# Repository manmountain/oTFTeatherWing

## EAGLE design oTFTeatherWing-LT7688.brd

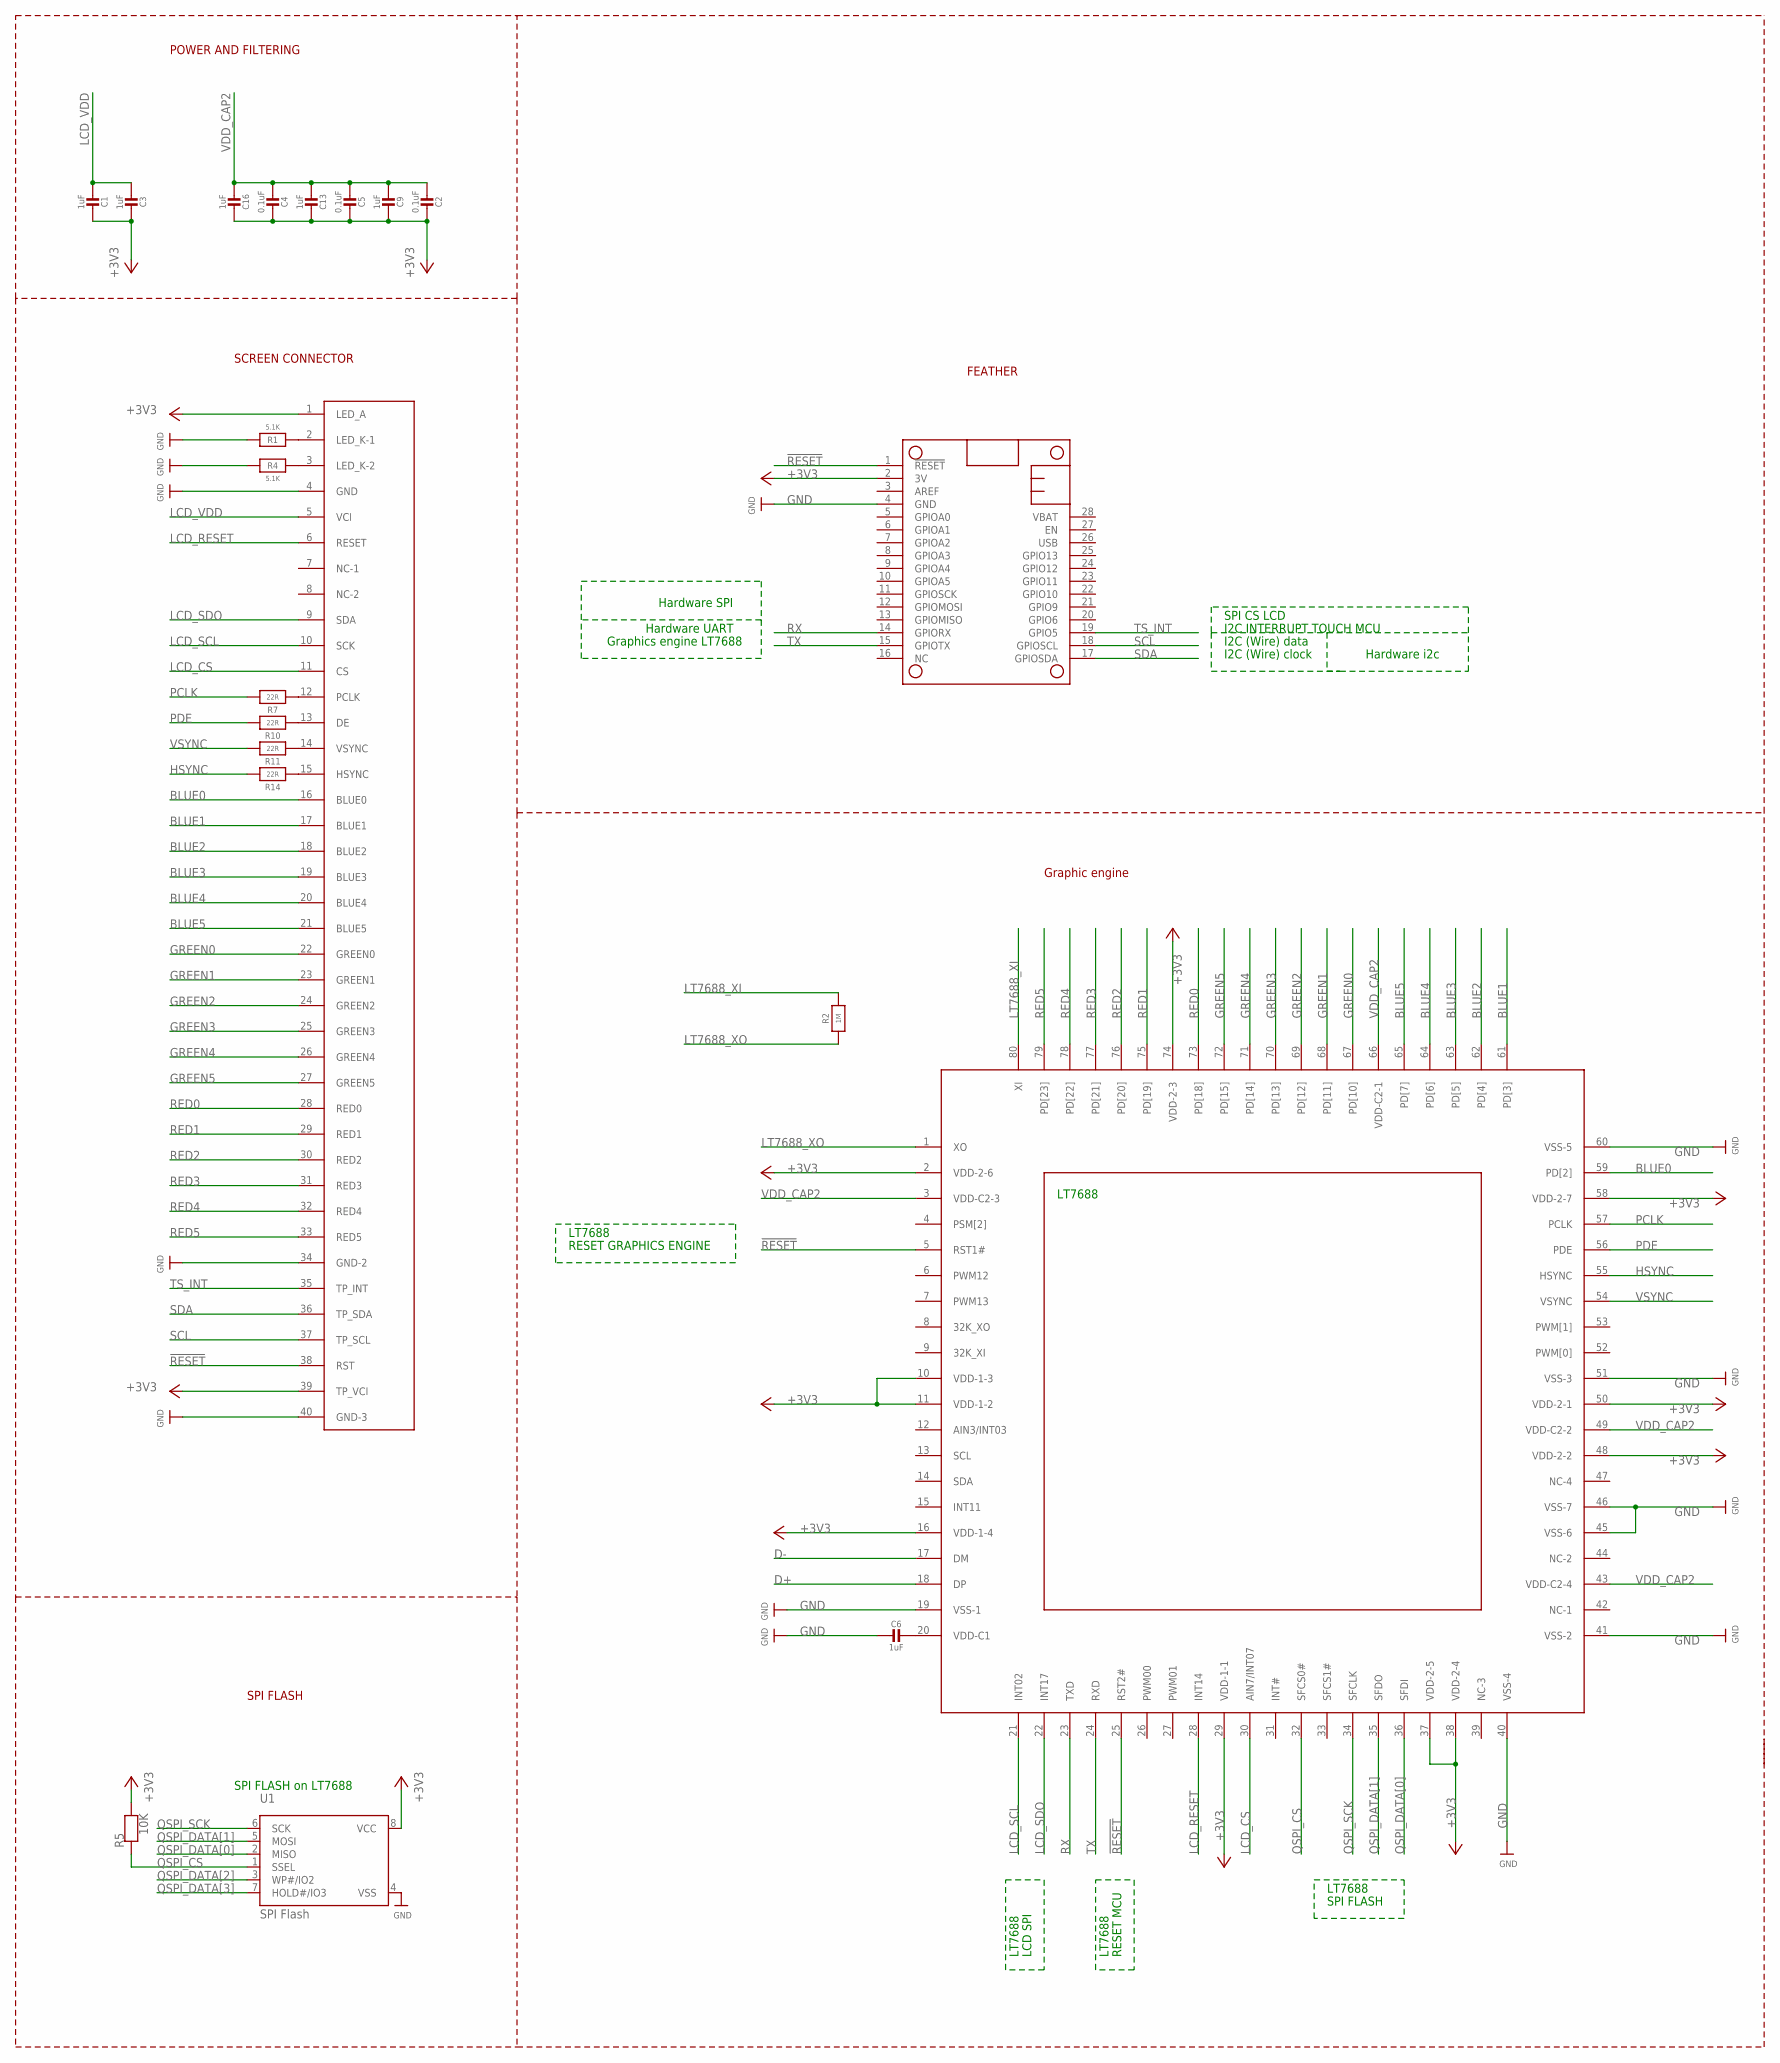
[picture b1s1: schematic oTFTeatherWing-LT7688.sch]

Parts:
C1, C3, C6, C9, C13, C16: 1uF; 0603-NO
C2, C4, C5: 0.1uF; 0603-NO
MS2: FEATHERWING
R1, R4: 5.1K; 0603-NO
R2: 1M; 0603-NO
R5: 10K; 0603-NO
R7, R10, R11, R14: 22R; 0603-NO
U1: SPI Flash; USON8
U$1: LT7688; QFN40P900X900X70-81T710N
U$2: FPC-LCD; XF2M-4015-1F-REVERSE

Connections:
!RESET: MS2.1 (!RESET), U$1.5 (RST1#), U$1.25 (RST2#), U$2.38 (RST)
+3V3: C1.1, C2.1, C3.1, C4.1, C5.1, C9.1, C13.1, C16.1, MS2.2 (3V), R5.2, U1.8 (VCC), U$1.2 (VDD-2-6), U$1.10 (VDD-1-3), U$1.11 (VDD-1-2), U$1.16 (VDD-1-4), U$1.29 (VDD-1-1), U$1.37 (VDD-2-5), U$1.38 (VDD-2-4), U$1.48 (VDD-2-2), U$1.50 (VDD-2-1), U$1.58 (VDD-2-7), U$1.74 (VDD-2-3), U$2.1 (LED_A), U$2.39 (TP_VCI)
BLUE0: U$1.59 (PD[2]), U$2.16 (BLUE0)
BLUE1: U$1.61 (PD[3]), U$2.17 (BLUE1)
BLUE2: U$1.62 (PD[4]), U$2.18 (BLUE2)
BLUE3: U$1.63 (PD[5]), U$2.19 (BLUE3)
BLUE4: U$1.64 (PD[6]), U$2.20 (BLUE4)
BLUE5: U$1.65 (PD[7]), U$2.21 (BLUE5)
D+: U$1.18 (DP)
D-: U$1.17 (DM)
GND: C6.2, MS2.4 (GND), R1.1, R4.1, U1.4 (VSS), U$1.19 (VSS-1), U$1.40 (VSS-4), U$1.41 (VSS-2), U$1.45 (VSS-6), U$1.46 (VSS-7), U$1.51 (VSS-3), U$1.60 (VSS-5), U$2.4 (GND), U$2.34 (GND-2), U$2.40 (GND-3)
GREEN0: U$1.67 (PD[10]), U$2.22 (GREEN0)
GREEN1: U$1.68 (PD[11]), U$2.23 (GREEN1)
GREEN2: U$1.69 (PD[12]), U$2.24 (GREEN2)
GREEN3: U$1.70 (PD[13]), U$2.25 (GREEN3)
GREEN4: U$1.71 (PD[14]), U$2.26 (GREEN4)
GREEN5: U$1.72 (PD[15]), U$2.27 (GREEN5)
HSYNC: R14.2, U$1.55 (HSYNC)
LCD_CS: U$1.30 (AIN7/INT07), U$2.11 (CS)
LCD_RESET: U$1.28 (INT14), U$2.6 (RESET)
LCD_SCL: U$1.21 (INT02), U$2.10 (SCK)
LCD_SDO: U$1.22 (INT17), U$2.9 (SDA)
LCD_VDD: C1.2, C3.2, U$2.5 (VCI)
LT7688_XI: R2.2, U$1.80 (XI)
LT7688_XO: R2.1, U$1.1 (XO)
unnamed: R1.2, U$2.2 (LED_K-1)
unnamed: C6.1, U$1.20 (VDD-C1)
unnamed: R4.2, U$2.3 (LED_K-2)
unnamed: R7.1, U$2.12 (PCLK)
unnamed: R10.1, U$2.13 (DE)
unnamed: R11.1, U$2.14 (VSYNC)
unnamed: R14.1, U$2.15 (HSYNC)
PCLK: R7.2, U$1.57 (PCLK)
PDE: R10.2, U$1.56 (PDE)
QSPI_CS: R5.1, U1.1 (SSEL), U$1.32 (SFCS0#)
QSPI_DATA[0]: U1.2 (MISO), U$1.36 (SFDI)
QSPI_DATA[1]: U1.5 (MOSI), U$1.35 (SFDO)
QSPI_DATA[2]: U1.3 (WP#/IO2)
QSPI_DATA[3]: U1.7 (HOLD#/IO3)
QSPI_SCK: U1.6 (SCK), U$1.34 (SFCLK)
RED0: U$1.73 (PD[18]), U$2.28 (RED0)
RED1: U$1.75 (PD[19]), U$2.29 (RED1)
RED2: U$1.76 (PD[20]), U$2.30 (RED2)
RED3: U$1.77 (PD[21]), U$2.31 (RED3)
RED4: U$1.78 (PD[22]), U$2.32 (RED4)
RED5: U$1.79 (PD[23]), U$2.33 (RED5)
RX: MS2.14 (GPIORX), U$1.23 (TXD)
SCL: MS2.18 (GPIOSCL), U$2.37 (TP_SCL)
SDA: MS2.17 (GPIOSDA), U$2.36 (TP_SDA)
TS_INT: MS2.19 (GPIO5), U$2.35 (TP_INT)
TX: MS2.15 (GPIOTX), U$1.24 (RXD)
VDD_CAP2: C2.2, C4.2, C5.2, C9.2, C13.2, C16.2, U$1.3 (VDD-C2-3), U$1.43 (VDD-C2-4), U$1.49 (VDD-C2-2), U$1.66 (VDD-C2-1)
VSYNC: R11.2, U$1.54 (VSYNC)

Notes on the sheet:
LT7688
POWER AND FILTERING
SPI CS LCD
I2C INTERRUPT TOUCH MCU
I2C (Wire) data
I2C (Wire) clock
Hardware i2c
Hardware UART
Graphics engine LT7688
Hardware SPI
RESET MCU
RESET GRAPHICS ENGINE
SPI FLASH
FEATHER
SCREEN CONNECTOR
Graphic engine
SPI FLASH on LT7688
LCD SPI

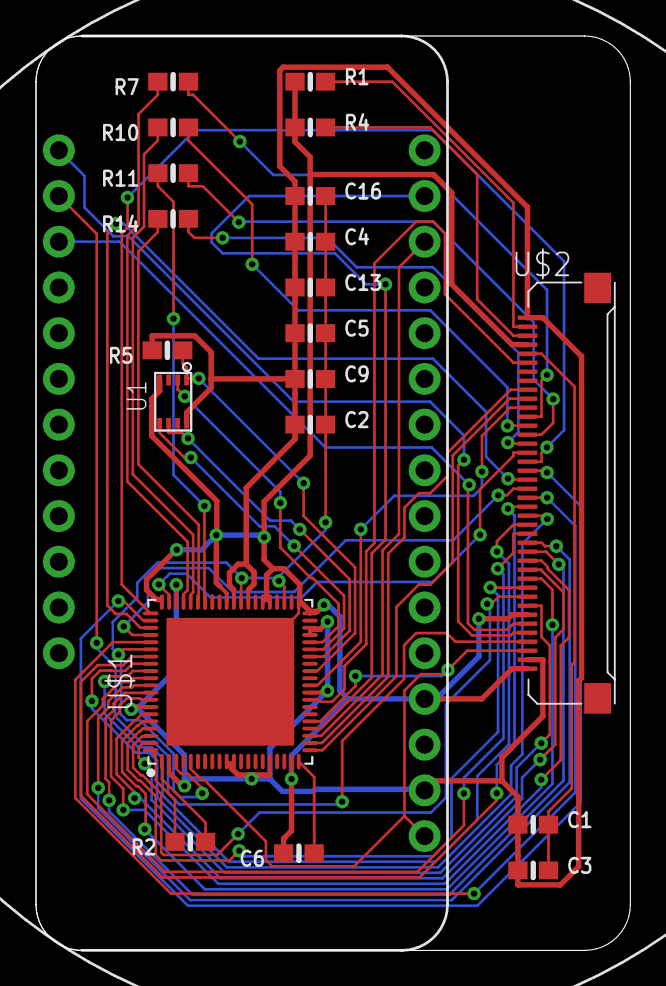
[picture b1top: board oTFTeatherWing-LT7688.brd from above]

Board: 2 copper layers, 33.0 x 50.8 mm, 21 parts (0 on the bottom side), 49 nets.

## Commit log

2021-01-26 forgot pdf schematic
2021-01-28 minor fixes
2021-01-28 added library for symbols/footprints for screen connector and lt7688
2021-01-28 changed lcd spi to lt7688
